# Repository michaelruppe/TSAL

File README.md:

# TSAL
A comparator-based TSAL design for FSAE Electric 2019

This repo has been moved [here](https://github.com/michaelruppe/FSAE)

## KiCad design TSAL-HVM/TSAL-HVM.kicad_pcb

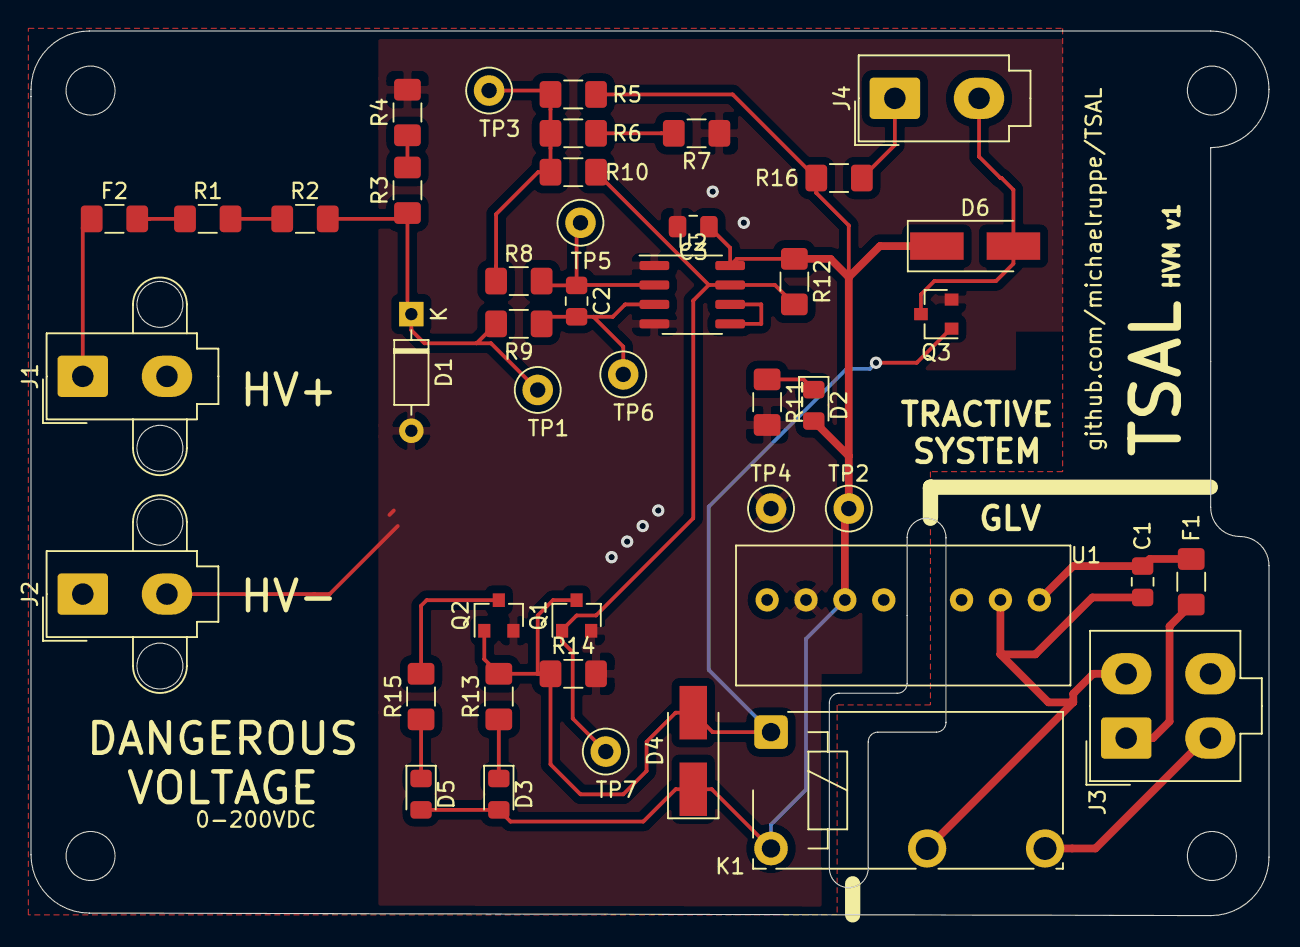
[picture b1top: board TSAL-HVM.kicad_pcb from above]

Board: 2 copper layers, 80.9 x 57.8 mm, 44 parts (0 on the bottom side), 24 nets.

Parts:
C1: 1u; C_0805_2012Metric_Pad1.15x1.40mm_HandSolder
C2: 10n; C_0805_2012Metric_Pad1.15x1.40mm_HandSolder
C3: 100n; C_0805_2012Metric_Pad1.15x1.40mm_HandSolder
D1: 12V; D_DO-35_SOD27_P7.62mm_Horizontal
D2: PWR; LED_0805_2012Metric_Pad1.15x1.40mm_HandSolder
D3: VLO; LED_0805_2012Metric_Pad1.15x1.40mm_HandSolder
D4, D6: D; D_SMA_Handsoldering
D5: VHI; LED_0805_2012Metric_Pad1.15x1.40mm_HandSolder
F1, F2: Fuse_Small; Fuse_1206_3216Metric_Pad1.42x1.75mm_HandSolder
J1: HV+; Molex_Mini-Fit_Jr_5566-02A2_2x01_P4.20mm_Vertical
J2: HV-; Molex_Mini-Fit_Jr_5566-02A2_2x01_P4.20mm_Vertical
J3: Conn_01x03_Male; Molex_Mini-Fit_Jr_5566-04A_2x02_P4.20mm_Vertical
J4: VHI; Molex_Mini-Fit_Jr_5566-02A_2x01_P4.20mm_Vertical
K1: TE_PCH-1xxx2M; Relay_SPST_TE_PCH-1xxx2M
Q1, Q2, Q3: 2N7002; SOT-23
R1, R2: 499k; R_1206_3216Metric_Pad1.42x1.75mm_HandSolder
R3: 49k9; R_1206_3216Metric_Pad1.42x1.75mm_HandSolder
R4, R11, R13, R15: 2k2; R_1206_3216Metric_Pad1.42x1.75mm_HandSolder
R5: 75k; R_1206_3216Metric_Pad1.42x1.75mm_HandSolder
R6, R12, R14: 24k; R_1206_3216Metric_Pad1.42x1.75mm_HandSolder
R7: 900; R_1206_3216Metric_Pad1.42x1.75mm_HandSolder
R8, R9: 100; R_1206_3216Metric_Pad1.42x1.75mm_HandSolder
R10: 1M; R_1206_3216Metric_Pad1.42x1.75mm_HandSolder
R16: PRV; R_1206_3216Metric_Pad1.42x1.75mm_HandSolder
TP1, TP3, TP5, TP6, TP7: TestPoint; TestPoint_Loop_D1.80mm_Drill1.0mm_Beaded
TP2: +12; TestPoint_Loop_D1.80mm_Drill1.0mm_Beaded
TP4: GND; TestPoint_Loop_D1.80mm_Drill1.0mm_Beaded
U1: SPAN02A-12; SPAN02
U2: LM311; SOIC-8_3.9x4.9mm_P1.27mm

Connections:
+12V: C3.1, D2.2, D3.2, D4.1, D5.2, D6.1, K1.5, R5.2, R12.1, R16.1, TP2.1, U1.6, U2.8
+Vin: F1.1, J3.1
-Vin: C1.2, J3.2, K1.2, U1.2
/+HV: F2.1, J1.1
GND: C3.2, D1.2, J2.2, Q1.2, Q2.2, Q3.2, R4.2, R7.1, R11.2, R14.2, TP4.1, U1.7, U2.1, U2.4
unnamed: C1.1, F1.2, U1.1
unnamed: C2.1, R8.1, TP5.1, U2.2
unnamed: C2.2, R9.1, TP6.1, U2.3
unnamed: D1.1, R2.2, R3.1, R9.2, TP1.1
unnamed: D2.1, R11.1
unnamed: D3.1, R13.1
unnamed: D4.2, K1.1, Q1.3, Q2.1, Q3.1, R13.2, R14.1
unnamed: D5.1, R15.1
unnamed: D6.2, J4.2, Q3.3
unnamed: F2.2, R1.1
unnamed: J4.1, R16.2
unnamed: Q1.1, R10.2, R12.2, TP7.1, U2.7
unnamed: Q2.3, R15.2
unnamed: R1.2, R2.1
unnamed: R3.2, R4.1
unnamed: R6.1, R7.2
unnamed: R5.1, R6.2, R8.2, R10.1, TP3.1
unnamed: U2.5, U2.6
OUT: J3.3, K1.3

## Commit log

2019-08-08 Update README.md
    add spec table
2019-08-08 Update README.md
    fix typo in spec table
2019-08-12 Rev 1 build
2019-08-12 Update readme. Add graphics and description of modules
